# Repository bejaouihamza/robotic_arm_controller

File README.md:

# 🦾 6-Axis Robotic Arm Controller — RP2040

> A high-performance embedded controller for 6-axis robotic arms featuring PIO-based jitter-free PWM, per-channel current sensing, real-time torque estimation, and hardware-level collision detection — no external sensors required.

---

## 📸 PCB Renders

| 3D Render | PCB Layout | Schematic |
|:---------:|:----------:|:---------:|
|  |  |  |

---

## ⚡ Key Specs

| Parameter | Value |
|-----------|-------|
| MCU | Raspberry Pi RP2040 — Dual-core ARM Cortex-M0+ @ 133 MHz |
| Flash | 16MB W25Q16JV55 QSPI |
| Servo Channels | 6 independent, PIO-generated PWM |
| PWM Frequency | 50 Hz · 500–2500 µs pulse range |
| PWM Jitter | < 1 µs (PIO hardware, zero CPU involvement) |
| Current Sense | Per-channel INA180 amplifier (×20 gain, 10 mΩ shunt) |
| Peak Current | 10A total across all 6 channels |
| Input Voltage | 6V – 24V VIN + USB-C 5V |
| PCB | 4-Layer, KiCad |
| Firmware | MicroPython · C++ Pico SDK |
| License | CERN Open Hardware License v2 |

---

## 🧠 Core Concept

Traditional servo controllers simply send PWM signals. This board goes further:

```
MEASURE  →  ANALYZE  →  REACT
```

Every servo channel has a dedicated current sense amplifier. The RP2040 reads all six channels through a **74HC4051** analog multiplexer, continuously estimating torque, detecting collisions, and triggering per-channel shutdowns — all in real time.

---

## 🔩 Hardware & Components

### Processing Unit
- **RP2040** — Dual-core ARM Cortex-M0+ @ 133 MHz, 264KB SRAM, 8 PIO state machines
- **W25Q16JV55** — 16MB QSPI Flash for firmware and data logging
- **12 MHz Crystal** — Stable PLL reference for USB timing and precise PWM periods

### Power Management
- **Integrated 5V Buck Converter** — Logic supply and low-power servo rail
- **AMS1117-3.3** — Clean LDO for MCU and all analog circuitry
- **Auto power-path** — Seamless switching between USB-C (5V) and external VIN (6–24V)

### Servo Driver Block (×6 channels)
- **AO3401A P-MOSFET** — High-side switch per channel. Enables software-controlled power sequencing and instant per-joint emergency stops
- **INA180A1** — Current sense amplifier, gain ×20. Amplifies shunt voltage for ADC reading
- **10 mΩ Shunt Resistor** — In-series with each servo rail for current measurement

### Analog Signal Chain
- **74HC4051** — 8:1 CMOS analog multiplexer. Funnels all 6 current sense signals into a single ADC pin using only 3 GPIO select lines
- **JP1–JP6 Jumpers** — Per-channel voltage selection: position A = 5V buck, position B = direct VIN

### User Interface
- **RV1, RV2** — 10kΩ potentiometers mapped to Joint 1 & 2 for manual testing
- **D3** — User-programmable LED
- **Reset button** — Hardware reset
- **SWD header** — ARM Serial Wire Debug (J-Link / DAPLink / OpenOCD)

---

## 🔌 GPIO Pin Mapping

> GPIO 0–5 → Servo **Enable** (P-MOS high-side switches)  
> GPIO 6–11 → Servo **PWM** (PIO state machine outputs)

| GPIO | Net Name | Type | Connected To | Description |
|------|----------|------|--------------|-------------|
| GPIO 0 | servo1_EN | GPIO OUT | AO3401A Gate Ch1 | High-side MOSFET enable — active HIGH |
| GPIO 1 | servo2_EN | GPIO OUT | AO3401A Gate Ch2 | High-side MOSFET enable — active HIGH |
| GPIO 2 | servo3_EN | GPIO OUT | AO3401A Gate Ch3 | High-side MOSFET enable — active HIGH |
| GPIO 3 | servo4_EN | GPIO OUT | AO3401A Gate Ch4 | High-side MOSFET enable — active HIGH |
| GPIO 4 | servo5_EN | GPIO OUT | AO3401A Gate Ch5 | High-side MOSFET enable — active HIGH |
| GPIO 5 | servo6_EN | GPIO OUT | AO3401A Gate Ch6 | High-side MOSFET enable — active HIGH |
| GPIO 6 | servo1_PWM | PIO OUT | Servo 1 signal wire | 50 Hz PIO PWM — sub-µs jitter |
| GPIO 7 | servo2_PWM | PIO OUT | Servo 2 signal wire | 50 Hz PIO PWM |
| GPIO 8 | servo3_PWM | PIO OUT | Servo 3 signal wire | 50 Hz PIO PWM |
| GPIO 9 | servo4_PWM | PIO OUT | Servo 4 signal wire | 50 Hz PIO PWM |
| GPIO 10 | servo5_PWM | PIO OUT | Servo 5 signal wire | 50 Hz PIO PWM |
| GPIO 11 | servo6_PWM | PIO OUT | Servo 6 signal wire | 50 Hz PIO PWM |
| GPIO 12 | S0 (MUX) | GPIO OUT | 74HC4051 Pin 11 | MUX address bit 0 |
| GPIO 13 | S1 (MUX) | GPIO OUT | 74HC4051 Pin 10 | MUX address bit 1 |
| GPIO 14 | S2 (MUX) | GPIO OUT | 74HC4051 Pin 9 | MUX address bit 2 |
| GPIO 18 | POT_1 | ADC0 IN | RV1 wiper | Manual Joint 1 input (0–3.3V = 0°–180°) |
| GPIO 19 | POT_2 | ADC1 IN | RV2 wiper | Manual Joint 2 input |
| GPIO 26 | MUX_A | GPIO OUT | 74HC4051 Pin 11 | MUX address line A |
| GPIO 27 | MUX_B | GPIO OUT | 74HC4051 Pin 10 | MUX address line B |
| GPIO 28 | MUX_C | GPIO OUT | 74HC4051 Pin 9 | MUX address line C |
| GPIO 29 | ISNS_ADC | ADC3 IN | 74HC4051 Common (Z) | Reads selected channel current sense voltage |
| USB-C | USB_DP/DM | USB 1.1 | USB-C connector | UF2 bootloader + CDC serial debug |
| SWD | SWCLK/SWDIO | DEBUG | SWD header (JB) | ARM Serial Wire Debug |

---

## 🏗️ PCB — 4-Layer Stackup

| Layer | Function | Details |
|-------|----------|---------|
| **Layer 1 — Top** | Signal + Components | All SMD placement, fine-pitch routing (MCU, INA180, MUX) |
| **Layer 2 — GND** | Solid ground plane | Low-impedance return path, EMI shielding, heat spreading |
| **Layer 3 — Power** | Split power planes | 3.3V (MCU/sensors) · 5V (buck) · VIN (servo rails) |
| **Layer 4 — Bottom** | High-current traces | Servo power delivery, secondary signal routing |

A 4-layer design is essential here — with 6 servo channels switching simultaneously and up to 10A peak current, a 2-layer board would suffer from unacceptable EMI coupling and resistive heating.

---

## 📐 Physics — How It Works

### Motor Torque from Current

The fundamental relationship exploited by this board:

```
τ = Kₜ × I
```

A DC motor's torque is directly proportional to its armature current. `Kₜ` is the motor's torque constant (Nm/A). By measuring current through the INA180 shunt amplifiers, we measure torque — without any mechanical sensor.

### Current Sensing Chain

```
I (servo current)
  → V_shunt = I × R_shunt          (Ohm's Law across 10mΩ shunt)
  → V_out = V_shunt × 20           (INA180 ×20 amplification)
  → ADC = (V_out / 3.3V) × 65535  (RP2040 12-bit ADC)
  → I = (ADC / 65535 × 3.3) / (20 × 0.01)
```

At 2.5A (overload threshold): `V_shunt = 25mV → V_out = 500mV` — well within ADC range.

**Resolution:** ~0.25 mA per LSB → ~0.02 mNm torque resolution per LSB.

### Servo PWM Position Encoding

```
θ° = (t_pulse − 500µs) / 2000µs × 180°
```

| Pulse Width | Angle |
|-------------|-------|
| 500 µs | 0° |
| 1500 µs | 90° (centre) |
| 2500 µs | 180° |

The RP2040's PIO state machines generate these pulses in hardware — completely independent of the CPU clock, eliminating software-induced jitter that corrupts positional accuracy.

### Why PIO Instead of Hardware PWM?

Hardware PWM slices share a clock divider. Reprogramming multiple channels simultaneously causes brief glitches. PIO state machines run from dedicated instruction memory, each executing its PWM loop independently — giving 6 perfectly phase-stable signals while freeing both CPU cores for inverse kinematics or vision tasks.

### Collision Detection — Torque Spike

When the arm hits an obstacle, the motor stalls. A stalled motor draws its locked-rotor current — far above normal running current:

```
Normal:  I ≈ 0.3–0.8 A  →  τ ≈ 0.025–0.068 Nm
Stall:   I → 2–4 A      →  τ → 0.17–0.34 Nm  ← triggers shutdown
```

The ADC scans all 6 channels continuously. A torque spike is detected within one scan cycle (~1 ms). The P-MOSFET cuts power within a single GPIO toggle (~10 ns).

---

## 🛡️ Safety System

| Feature | Description |
|---------|-------------|
| **Torque Estimation** | τ = Kₜ × I, live on all 6 joints, ~0.02 mNm resolution |
| **Collision Detection** | Configurable torque threshold (default 0.20 Nm) triggers per-joint shutdown |
| **Overcurrent Protection** | Sustained current > 2.5A sets latching fault, cuts P-MOSFET |
| **Emergency Stop** | All 6 channels cut simultaneously via single function call |
| **Smooth Motion** | Interpolated moves with per-step collision check |
| **Power Sequencing** | Staggered joint enable (100ms delay) prevents inrush brownout |
| **Fault Latch** | Fault persists until software reset — prevents repeated thermal stress |

---

## 💻 Firmware

```python
# robotic_arm_controller.py
# GPIO 0-5  → Servo ENABLE (P-MOS high-side switches)
# GPIO 6-11 → Servo PWM    (PIO state machines)
import rp2, machine, time

SERVO_EN_PINS  = [0, 1, 2, 3, 4, 5]
SERVO_PWM_PINS = [6, 7, 8, 9, 10, 11]
MUX_SEL_PINS   = [12, 13, 14]
ADC_ISNS_PIN   = 29
POT1_PIN, POT2_PIN = 18, 19

SERVO_MIN_US = 500
SERVO_MAX_US = 2500
ISNS_GAIN    = 20
SHUNT_R      = 0.010
OVERLOAD_A   = 2.5
KT_NM_PER_A  = 0.085
COLLISION_NM = 0.20

@rp2.asm_pio(sideset_init=rp2.PIO.OUT_LOW)
def servo_pwm_pio():
    pull(block)          .side(0)
    mov(x, osr)
    label("high_loop")
    jmp(x_dec, "high_loop")  .side(1)
    pull(block)          .side(1)
    mov(x, osr)
    label("low_loop")
    jmp(x_dec, "low_loop")   .side(0)

class ServoChannel:
    def __init__(self, en_pin, pwm_pin, sm_id):
        self.en = machine.Pin(en_pin, machine.Pin.OUT, value=0)
        self.sm = rp2.StateMachine(sm_id, servo_pwm_pio,
                    freq=2_000_000, sideset_base=machine.Pin(pwm_pin))
        self.sm.active(1)
        self.angle = 90
        self.set_angle(90)

    def power_on(self):  self.en.value(1)
    def power_off(self): self.en.value(0)

    def set_angle(self, deg):
        deg = max(0.0, min(180.0, float(deg)))
        us  = SERVO_MIN_US + (deg / 180.0) * (SERVO_MAX_US - SERVO_MIN_US)
        self.sm.put(int(us * 2))
        self.sm.put(int((20000 - us) * 2))
        self.angle = deg

class CurrentSensor:
    def __init__(self):
        self.mux = [machine.Pin(p, machine.Pin.OUT) for p in MUX_SEL_PINS]
        self.adc = machine.ADC(ADC_ISNS_PIN)

    def read_channel(self, ch):
        for i, pin in enumerate(self.mux):
            pin.value((ch >> i) & 1)
        time.sleep_us(5)
        v = (self.adc.read_u16() / 65535) * 3.3
        return round(v / (ISNS_GAIN * SHUNT_R), 4)

    def read_all(self):
        return [self.read_channel(i) for i in range(6)]

class RoboticArm:
    def __init__(self):
        self.joints = [ServoChannel(SERVO_EN_PINS[i], SERVO_PWM_PINS[i], i) for i in range(6)]
        self.isns   = CurrentSensor()
        self.pot1   = machine.ADC(POT1_PIN)
        self.pot2   = machine.ADC(POT2_PIN)
        self.fault  = [False] * 6

    def power_up_sequence(self, delay_ms=100):
        for j in self.joints:
            j.power_on()
            time.sleep_ms(delay_ms)

    def emergency_stop(self):
        for j in self.joints: j.power_off()
        print("[E-STOP] All channels cut")

    def move_to(self, angles):
        for i, (j, deg) in enumerate(zip(self.joints, angles)):
            if not self.fault[i]: j.set_angle(deg)

    def torque_estimate(self):
        return [round(a * KT_NM_PER_A, 4) for a in self.isns.read_all()]

    def detect_collision(self, threshold_nm=COLLISION_NM):
        hits = []
        for i, t in enumerate(self.torque_estimate()):
            if t > threshold_nm and not self.fault[i]:
                self.joints[i].power_off()
                self.fault[i] = True
                hits.append(i)
                print(f"[COLLISION] Joint {i+1} @ {t:.4f} Nm")
        return hits

    def check_overload(self):
        for i, a in enumerate(self.isns.read_all()):
            if a > OVERLOAD_A and not self.fault[i]:
                self.joints[i].power_off()
                self.fault[i] = True
                print(f"[FAULT] Joint {i+1} overcurrent: {a:.3f} A")

    def smooth_move(self, targets, steps=50, delay_ms=10):
        start = [j.angle for j in self.joints]
        for s in range(1, steps + 1):
            t = s / steps
            self.move_to([start[i] + t * (targets[i] - start[i]) for i in range(6)])
            self.check_overload()
            if self.detect_collision(): return False
            time.sleep_ms(delay_ms)
        return True

    def read_manual(self):
        return (round((self.pot1.read_u16() / 65535) * 180, 1),
                round((self.pot2.read_u16() / 65535) * 180, 1))

    def status(self):
        c = self.isns.read_all()
        t = self.torque_estimate()
        print(f"{'Joint':<8}{'Angle':>8}{'Current':>10}{'Torque':>10}{'State':>8}")
        print("-" * 46)
        for i in range(6):
            print(f"J{i+1:<7}{self.joints[i].angle:>7.1f}°{c[i]:>9.3f}A{t[i]:>9.4f}Nm{'FAULT' if self.fault[i] else 'OK':>8}")

# ── Main ──────────────────────────────────────────────────
arm = RoboticArm()
arm.power_up_sequence(delay_ms=120)
arm.smooth_move([90, 90, 90, 90, 90, 90])

while True:
    j1, j2 = arm.read_manual()
    arm.move_to([j1, j2, 90, 90, 90, 90])
    arm.check_overload()
    arm.detect_collision()
    arm.status()
    time.sleep_ms(20)
```

---

## 🚀 Getting Started

**1. Power the board**
Connect VIN (6–24V) to the screw terminal. Set jumpers JP1–JP6:
- Position **A** → 5V internal buck (standard hobby servos)
- Position **B** → Direct VIN (high-torque servos above 7.4V)

**2. Flash firmware**
Hold `BOOT` on the back, press `RESET`. A drive named `RPI-RP2` appears. Drag your `.uf2` file onto it. Board reboots and runs automatically.

**3. Test with potentiometers**
RV1 and RV2 control Joint 1 and Joint 2 by default. Rotate to verify servo response before connecting the full arm.

**4. Monitor over serial**
Open any terminal at **115200 baud** on the USB-C port. `arm.status()` prints a live table of angle, current, torque, and fault state for all 6 joints.

**5. Tune collision thresholds**
Run the arm freely and log `status()` output. Set `COLLISION_NM` to ~1.5–2× the maximum torque observed during normal free movement.

**6. Extend with C++ for performance**
Run motion control on Core 0 and current sensing on Core 1 for fully parallel deterministic operation. Core 1 can achieve scan rates exceeding 10 kHz — enabling sub-millisecond collision response.

---

## ✅ Capabilities

- 6 independent PIO-generated PWM channels — sub-microsecond jitter
- Real-time torque estimation on every joint — no mechanical sensors
- Per-channel collision detection with configurable threshold
- Individual high-side MOSFET shutdown per channel
- Emergency stop — all 6 channels cut within a single GPIO toggle
- Smooth interpolated motion with mid-move collision check
- Staggered power-up to prevent inrush brownout
- Manual joint control via onboard potentiometers
- USB-C UF2 flashing — no external programmer required
- SWD debug header — J-Link / DAPLink / OpenOCD compatible
- Dual-core execution: motion on Core 0, sensing on Core 1
- MicroPython and C++ Pico SDK fully supported
- Per-servo independent voltage selection via JP1–JP6
- Live status table: angle, current, torque, fault per joint
- Latching fault system with software reset
- CERN Open Hardware License — free to modify and manufacture

---

## 📄 License

Released under the **CERN Open Hardware Licence Version 2 — Strongly Reciprocal (CERN-OHL-S v2)**.  
Free to study, modify, manufacture, and distribute — derivatives must remain open source.

---

<div align="center">Designed by <strong>B.H</strong></div>

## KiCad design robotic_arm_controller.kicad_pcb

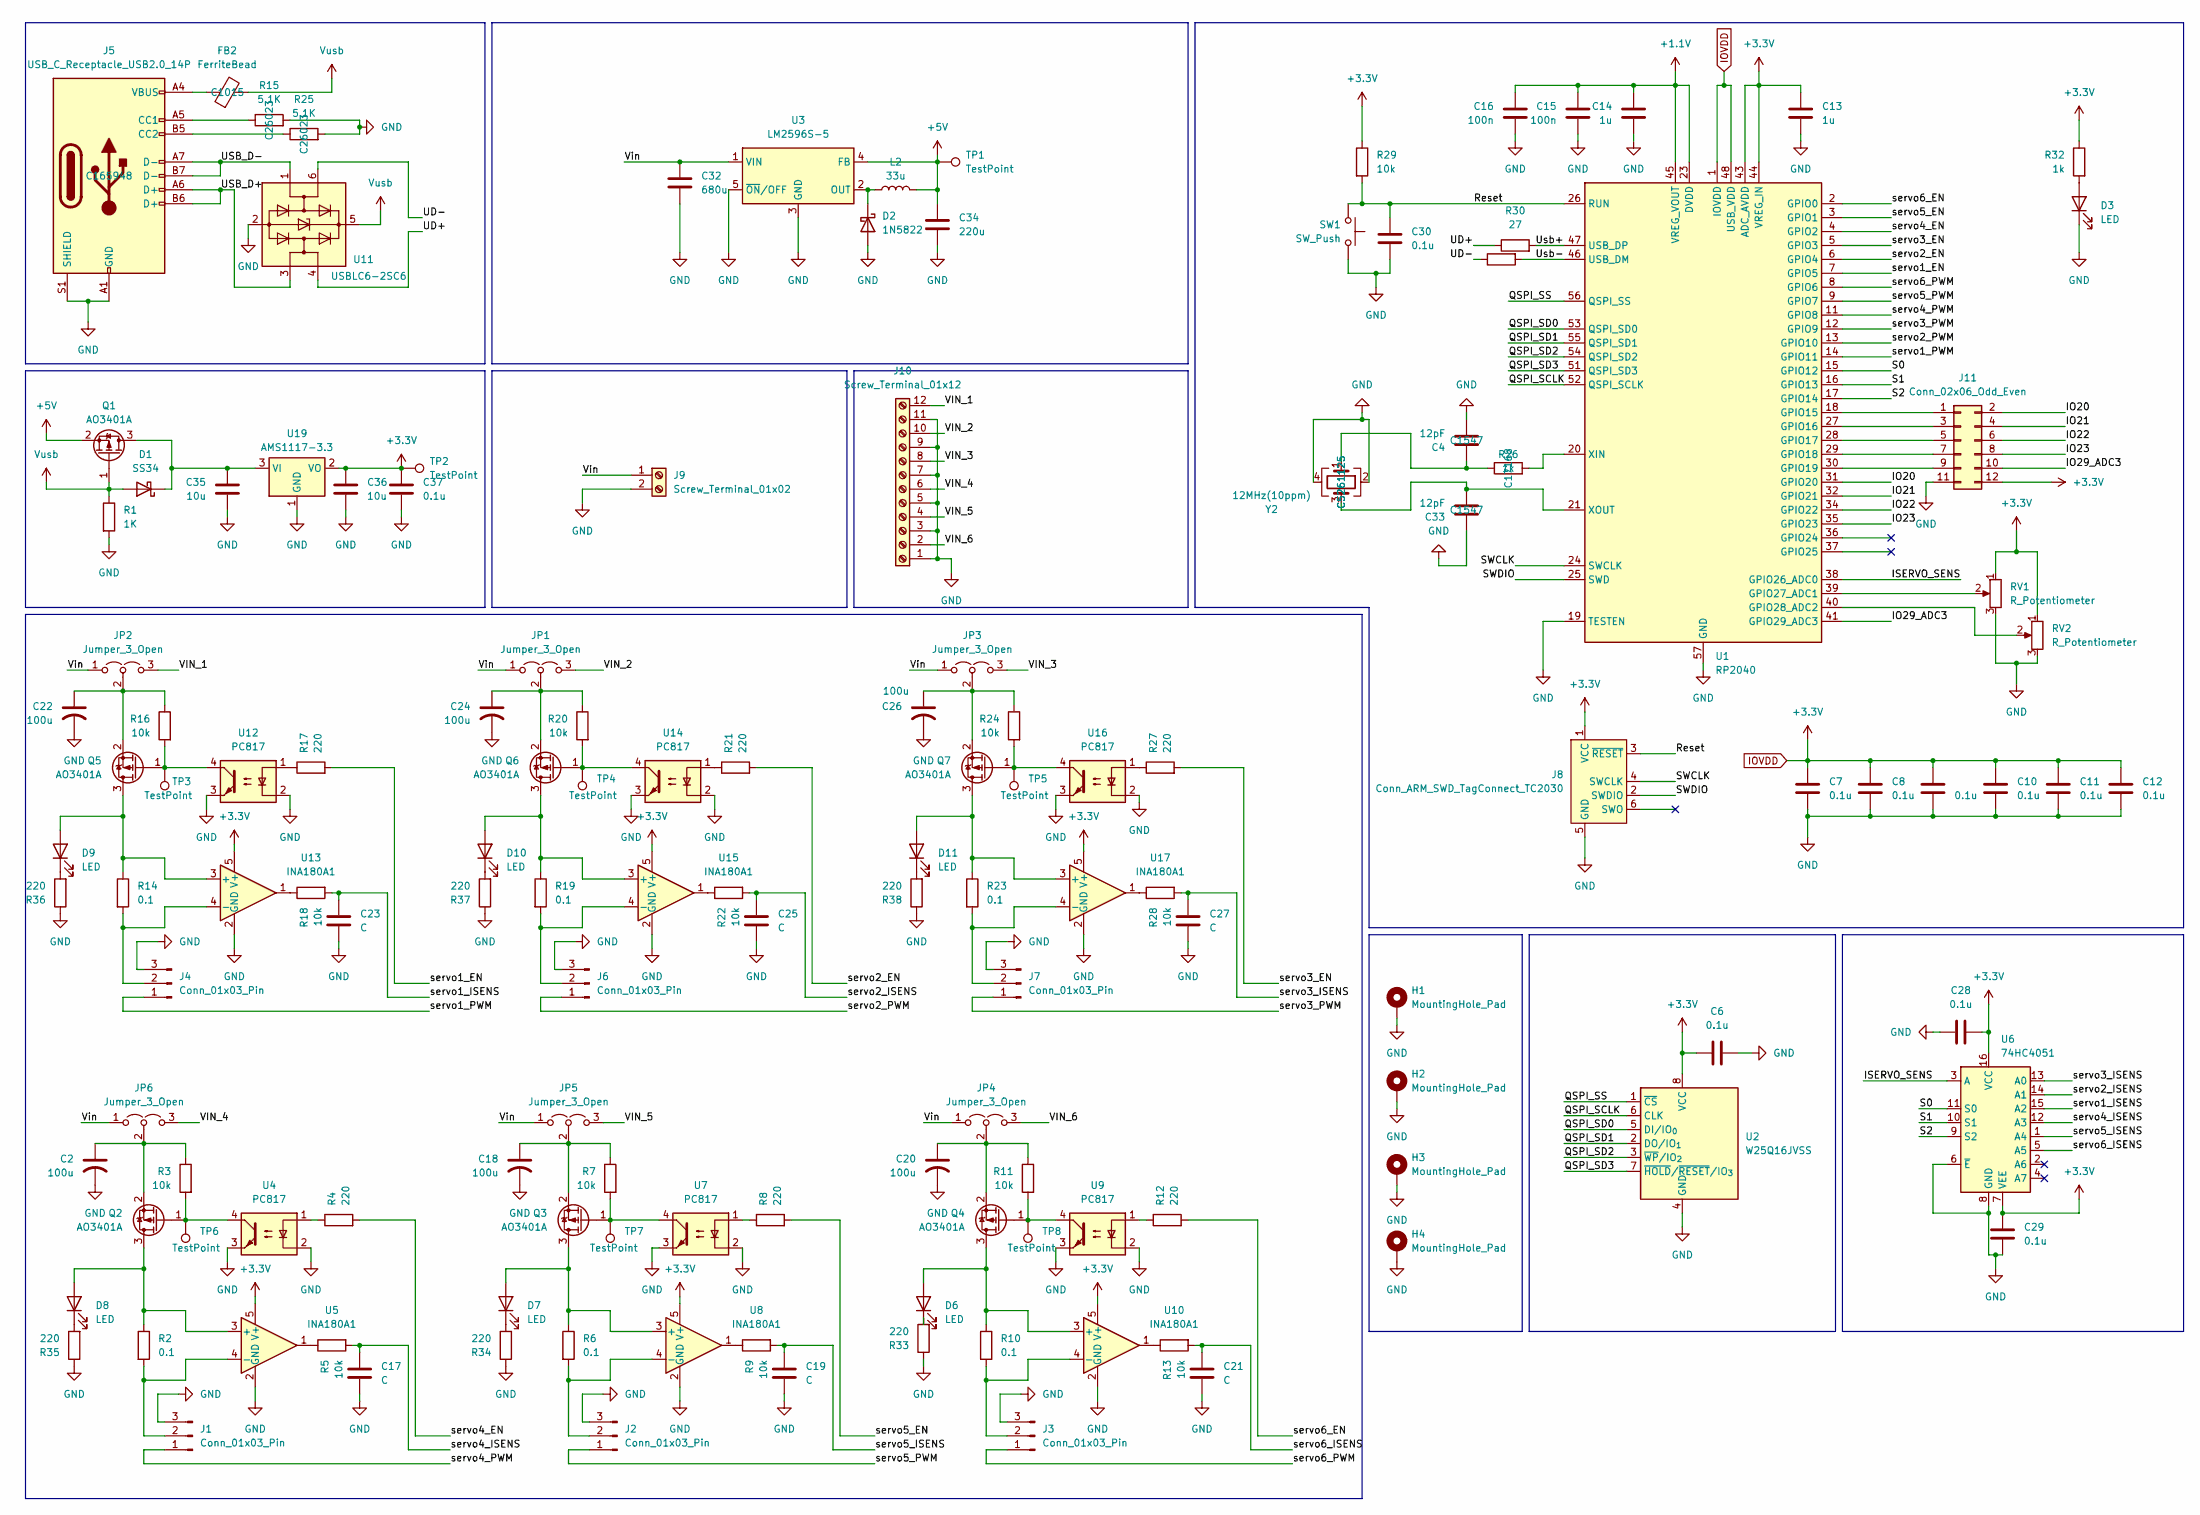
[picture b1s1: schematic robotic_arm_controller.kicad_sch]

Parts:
C2, C18, C20, C22, C24, C26: 100u; C_Radial_D5.0mm_H7.0mm_P2.00mm
C4, C33: 12pF; C_0402_1005Metric; MNF PART NUMBER C1547; LCSC Part # C1547
C6, C28, C29, C30, C37: 0.1u; C_1206_3216Metric
C7, C8, C9, C10, C11, C12: 0.1u; C_0603_1608Metric
C13, C14: 1u; C_0603_1608Metric
C15, C16: 100n; C_0603_1608Metric
C17, C19, C21, C23, C25, C27: C; C_1206_3216Metric
C32: 680u; C_Elec_10x10.2
C34: 220u; C_Elec_10x10.2
C35: 10u; C_Elec_10x10.2
C36: 10u; C_1206_3216Metric
D1: SS34; D_SMA
D2: 1N5822; D_SMB
D3, D6, D7, D8, D9, D10, D11: LED; LED_0805_2012Metric
FB2: FerriteBead; L_0805_2012Metric; LCSC Part # C1015
H1, H2, H3, H4: MountingHole_Pad; MountingHole_2.5mm_Pad_Via
J1, J2, J3, J4, J6, J7: Conn_01x03_Pin; PinHeader_1x03_P2.54mm_Vertical
J5: USB_C_Receptacle_USB2.0_14P; USB_C_Receptacle_HRO_TYPE-C-31-M-12; LCSC Part # C165948
J8: Conn_ARM_SWD_TagConnect_TC2030; Tag-Connect_TC2030-IDC-FP_2x03_P1.27mm_Vertical
J9: Screw_Terminal_01x02; TerminalBlock_Phoenix_MKDS-1,5-2-5.08_1x02_P5.08mm_Horizont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
J10: Screw_Terminal_01x12; TerminalBlock_Phoenix_MKDS-1,5-12-5.08_1x12_P5.08mm_Horizon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
J11: Conn_02x06_Odd_Even; PinHeader_2x06_P2.54mm_Vertical_SMD
JP1, JP2, JP3, JP4, JP5, JP6: Jumper_3_Open; PinHeader_1x03_P2.54mm_Vertical
L2: 33u; L_Bourns_SRP1050WA
Q1, Q2, Q3, Q4, Q5, Q6, Q7: AO3401A; SOT-23
R1: 1K; R_0805_2012Metric
R2, R6, R10, R14, R19, R23: 0.1; R_2010_5025Metric
R3, R5, R7, R9, R11, R13, R16, R18, R20, R22, R24, R28, R29: 10k; R_0805_2012Metric
R4, R8, R12, R17, R21, R27, R33, R34, R35, R36, R37, R38: 220; R_0805_2012Metric
R15, R25: 5.1K; R_0805_2012Metric; LCSC Part # C26023
R26: 1k; R_0402_1005Metric; MNF PART NUMBER C17168; LCSC Part # C17168
R30, R31: 27; R_0603_1608Metric
R32: 1k; R_0805_2012Metric
RV1, RV2: R_Potentiometer; TRIM_PT01-B115D-B103
SW1: SW_Push; SW_PUSH_6mm_H5mm
TP1, TP2: TestPoint; TestPoint_Pad_D2.0mm
TP3, TP4, TP5, TP6, TP7, TP8: TestPoint; TestPoint_Keystone_5005-5009_Compact
U1: RP2040; QFN-56-1EP_7x7mm_P0.4mm_EP3.2x3.2mm
U2: W25Q16JVSS; SOIC-8_5.3x5.3mm_P1.27mm
U3: LM2596S-5; TO-263-5_TabPin3
U4, U7, U9, U12, U14, U16: PC817; Analog_KS-4
U5, U8, U10, U13, U15, U17: INA180A1; SOT-23-5
U6: 74HC4051; SOIC-16W_5.3x10.2mm_P1.27mm
U11: USBLC6-2SC6; SOT-23-6; Manufacturer_Part_Number USBLC6-2SC6; Mouser Part Number 511-USBLC6-2SC6
U19: AMS1117-3.3; SOT-223-3_TabPin2
Y2: 12MHz(10ppm); Crystal_SMD_2520-4Pin_2.5x2.0mm; MNF PART NUMBER C5261125; LCSC Part # C5261125

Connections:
+1.1V: C14.2, C15.2, C16.2, U1.23 (DVDD), U1.45 (VREG_VOUT), U1.50 (DVDD)
+5V: C34.1, L2.2, Q1.2 (S), TP1.1, U3.4 (FB)
/IO20: J11.2, U1.31 (GPIO20)
/IO21: J11.4, U1.32 (GPIO21)
/IO22: J11.6, U1.34 (GPIO22)
/IO23: J11.8, U1.35 (GPIO23)
/IO29_ADC3: J11.10, U1.41 (GPIO29_ADC3)
/ISERVO_SENS: U1.38 (GPIO26_ADC0), U6.3 (A)
/QSPI_SCLK: U1.52 (QSPI_SCLK), U2.6 (CLK)
/QSPI_SD0: U1.53 (QSPI_SD0), U2.5 (DI/IO_{0})
/QSPI_SD1: U1.55 (QSPI_SD1), U2.2 (DO/IO_{1})
/QSPI_SD2: U1.54 (QSPI_SD2), U2.3 (~WP/IO_{2})
/QSPI_SD3: U1.51 (QSPI_SD3), U2.7 (~HOLD/~RESET/IO_{3})
/QSPI_SS: U1.56 (QSPI_SS), U2.1 (~CS)
/Reset: C30.2, J8.3 (~RESET), R29.2, SW1.2, U1.26 (RUN)
/S0: U1.15 (GPIO12), U6.11 (S0)
/S1: U1.16 (GPIO13), U6.10 (S1)
/S2: U1.17 (GPIO14), U6.9 (S2)
/SWCLK: J8.4 (SWCLK), U1.24 (SWCLK)
/SWDIO: J8.2 (SWDIO), U1.25 (SWD)
/UD+: R30.1, U11.4 (I/O2)
/UD-: R31.1, U11.6 (I/O1)
/USB_D+: J5.A6 (D+), J5.B6 (D+), U11.3 (I/O2)
/USB_D-: J5.A7 (D-), J5.B7 (D-), U11.1 (I/O1)
/Usb+: R30.2, U1.47 (USB_DP)
/Usb-: R31.2, U1.46 (USB_DM)
/VIN_1: J10.12, JP2.3 (B)
/VIN_2: J10.10, JP1.3 (B)
/VIN_3: J10.8, JP3.3 (B)
/VIN_4: J10.6, JP6.3 (B)
/VIN_5: J10.4, JP5.3 (B)
/VIN_6: J10.2, JP4.3 (B)
/Vin: C32.1, J9.1, JP1.1 (A), JP2.1 (A), JP3.1 (A), JP4.1 (A), JP5.1 (A), JP6.1 (A), U3.1 (VIN)
/servo1_EN: R17.2, U1.7 (GPIO5)
/servo1_ISENS: C23.1, R18.2, U6.15 (A2)
/servo1_PWM: J4.1, U1.14 (GPIO11)
/servo2_EN: R21.2, U1.6 (GPIO4)
/servo2_ISENS: C25.1, R22.2, U6.14 (A1)
/servo2_PWM: J6.1, U1.13 (GPIO10)
/servo3_EN: R27.2, U1.5 (GPIO3)
/servo3_ISENS: C27.1, R28.2, U6.13 (A0)
/servo3_PWM: J7.1, U1.12 (GPIO9)
/servo4_EN: R4.2, U1.4 (GPIO2)
/servo4_ISENS: C17.1, R5.2, U6.12 (A3)
/servo4_PWM: J1.1, U1.11 (GPIO8)
/servo5_EN: R8.2, U1.3 (GPIO1)
/servo5_ISENS: C19.1, R9.2, U6.1 (A4)
/servo5_PWM: J2.1, U1.9 (GPIO7)
/servo6_EN: R12.2, U1.2 (GPIO0)
/servo6_ISENS: C21.1, R13.2, U6.5 (A5)
/servo6_PWM: J3.1, U1.8 (GPIO6)
GND: C2.2, C4.2, C6.2, C7.1, C8.1, C9.1, C10.1, C11.1, C12.1, C13.1, C14.1, C15.1, C16.1, C17.2, C18.2, C19.2, C20.2, C21.2, C22.2, C23.2, C24.2, C25.2, C26.2, C27.2, C28.1, C29.1, C30.1, C32.2, C33.1, C34.2, C35.2, C36.2, C37.2, D2.2 (A), D3.1 (K), H1.1, H2.1, H3.1, H4.1, J1.3, J2.3, J3.3, J4.3, J5.A1 (GND), J5.A12 (GND), J5.B1 (GND), J5.B12 (GND), J5.S1 (SHIELD), J6.3, J7.3, J8.5 (GND), J9.2, J10.1, J10.3, J10.5, J10.7, J10.9, J10.11, J11.11, R1.2, R15.2, R25.2, R33.1, R34.1, R35.1, R36.1, R37.1, R38.1, RV1.3, RV2.3, SW1.1, U1.19 (TESTEN), U1.57 (GND), U2.4 (GND), U3.3 (GND), U3.5 (~ON/OFF), U4.2, U4.3, U5.2 (GND), U6.6 (~E), U6.8 (GND), U7.2, U7.3, U8.2 (GND), U9.2, U9.3, U10.2 (GND), U11.2 (GND), U12.2, U12.3, U13.2 (GND), U14.2, U14.3, U15.2 (GND), U16.2, U16.3, U17.2 (GND), U19.1 (GND), Y2.2, Y2.4
IOVDD: C6.1, C7.2, C8.2, C9.2, C10.2, C11.2, C12.2, C13.2, C28.2, C29.2, C36.1, C37.1, J8.1 (VCC), J11.12, R29.1, R32.1, RV1.1, RV2.1, TP2.1, U1.1 (IOVDD), U1.10 (IOVDD), U1.22 (IOVDD), U1.33 (IOVDD), U1.42 (IOVDD), U1.43 (ADC_AVDD), U1.44 (VREG_IN), U1.48 (USB_VDD), U1.49 (IOVDD), U2.8 (VCC), U5.5 (V+), U6.7 (VEE), U6.16 (VCC), U8.5 (V+), U10.5 (V+), U13.5 (V+), U15.5 (V+), U17.5 (V+), U19.2 (VO)
unnamed: C4.1, R26.1, Y2.1
unnamed: C35.1, D1.1 (K), Q1.3 (D), U19.3 (VI)
unnamed: D2.1 (K), L2.1, U3.2 (OUT)
unnamed: D3.2 (A), R32.2
unnamed: D6.2 (A), Q4.3 (D), R10.1, U10.3 (+)
unnamed: D6.1 (K), R33.2
unnamed: D7.2 (A), Q3.3 (D), R6.1, U8.3 (+)
unnamed: D7.1 (K), R34.2
unnamed: D8.2 (A), Q2.3 (D), R2.1, U5.3 (+)
unnamed: D8.1 (K), R35.2
unnamed: D9.2 (A), Q5.3 (D), R14.1, U13.3 (+)
unnamed: D9.1 (K), R36.2
unnamed: D10.2 (A), Q6.3 (D), R19.1, U15.3 (+)
unnamed: D10.1 (K), R37.2
unnamed: D11.2 (A), Q7.3 (D), R23.1, U17.3 (+)
unnamed: D11.1 (K), R38.2
unnamed: FB2.1, J5.A4 (VBUS), J5.A9 (VBUS), J5.B4 (VBUS), J5.B9 (VBUS)
unnamed: J1.2, R2.2, U5.4 (-)
unnamed: J2.2, R6.2, U8.4 (-)
unnamed: J3.2, R10.2, U10.4 (-)
unnamed: J4.2, R14.2, U13.4 (-)
unnamed: J5.A5 (CC1), R15.1
unnamed: J5.B5 (CC2), R25.1
unnamed: J6.2, R19.2, U15.4 (-)
unnamed: J7.2, R23.2, U17.4 (-)
unnamed: J11.1, U1.18 (GPIO15)
unnamed: J11.3, U1.27 (GPIO16)
unnamed: J11.5, U1.28 (GPIO17)
unnamed: J11.7, U1.29 (GPIO18)
unnamed: J11.9, U1.30 (GPIO19)
unnamed: C24.1, JP1.2 (C), Q6.2 (S), R20.1
unnamed: C22.1, JP2.2 (C), Q5.2 (S), R16.1
unnamed: C26.1, JP3.2 (C), Q7.2 (S), R24.1
unnamed: C20.1, JP4.2 (C), Q4.2 (S), R11.1
unnamed: C18.1, JP5.2 (C), Q3.2 (S), R7.1
unnamed: C2.1, JP6.2 (C), Q2.2 (S), R3.1
unnamed: Q2.1 (G), R3.2, TP6.1, U4.4
unnamed: Q3.1 (G), R7.2, TP7.1, U7.4
unnamed: Q4.1 (G), R11.2, TP8.1, U9.4
unnamed: Q5.1 (G), R16.2, TP3.1, U12.4
unnamed: Q6.1 (G), R20.2, TP4.1, U14.4
unnamed: Q7.1 (G), R24.2, TP5.1, U16.4
unnamed: R4.1, U4.1
unnamed: R5.1, U5.1
unnamed: R8.1, U7.1
unnamed: R9.1, U8.1
unnamed: R12.1, U9.1
unnamed: R13.1, U10.1
unnamed: R17.1, U12.1
unnamed: R18.1, U13.1
unnamed: R21.1, U14.1
unnamed: R22.1, U15.1
unnamed: R27.1, U16.1
unnamed: R28.1, U17.1
unnamed: RV1.2, U1.39 (GPIO27_ADC1)
unnamed: RV2.2, U1.40 (GPIO28_ADC2)
unnamed: R26.2, U1.20 (XIN)
unnamed: C33.2, U1.21 (XOUT), Y2.3
Vusb: D1.2 (A), FB2.2, Q1.1 (G), R1.1, U11.5 (VBUS)

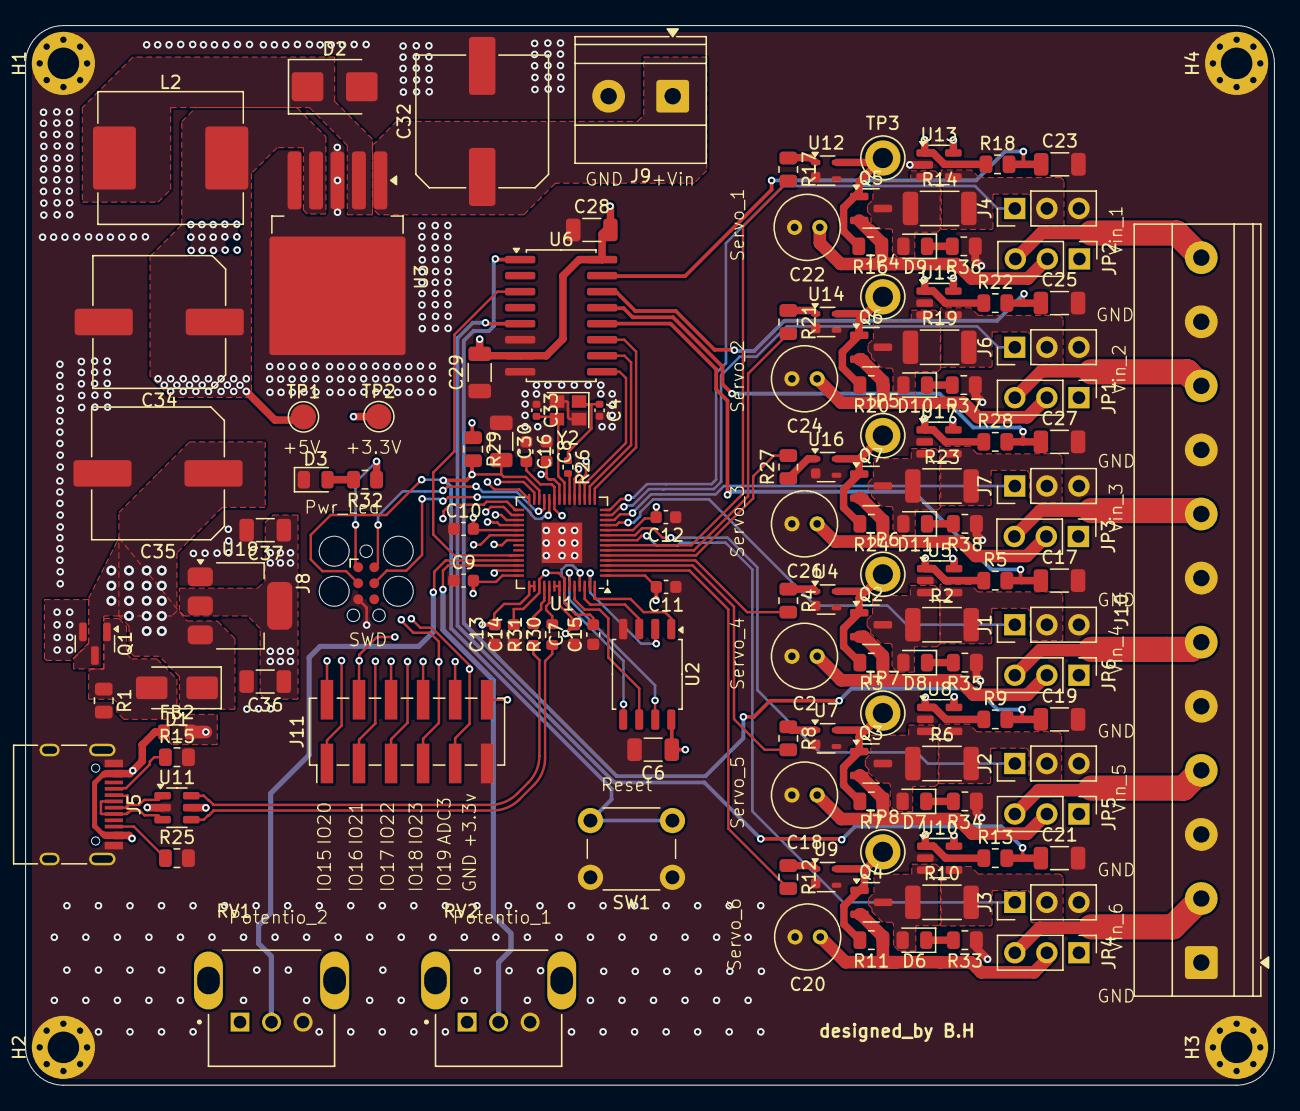
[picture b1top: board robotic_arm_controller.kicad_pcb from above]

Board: 4 copper layers, 99.0 x 84.0 mm, 140 parts (0 on the bottom side), 112 nets.

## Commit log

2026-04-10 Create servo6_control
2026-04-10 Change greeting from 'Hello' to 'Goodbye'
2026-04-10 Rename README.html to index.html
2026-04-11 Create README.md for robotic arm controller
    Add detailed README for 6-axis robotic arm controller including specifications, features, and setup instructions.

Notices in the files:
README.md:
License: CERN-OHL
